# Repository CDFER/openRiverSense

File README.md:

**openRiverSense - Water Quality Tester**
=====================================

### Overview

### Features

### Assembly

### Usage

### Improvements for V2

* Reduce interference between Battery Charging and GPS Antenna
* Backlight powered by CC buck power source?
* Better Shielding on Screen SPI bus to enable reliable 80Mhz bus speeds
* Improve GPS RTC backup power source (CR2032, direct from Lithium-ion)?

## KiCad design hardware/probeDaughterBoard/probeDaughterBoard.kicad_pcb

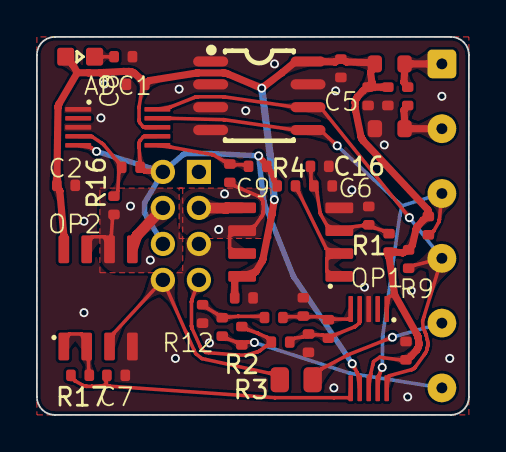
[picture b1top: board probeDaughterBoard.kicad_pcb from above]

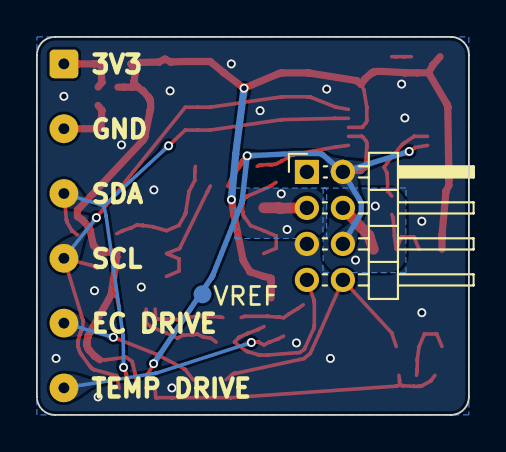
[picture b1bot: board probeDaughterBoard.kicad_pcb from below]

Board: 2 copper layers, 24.0 x 21.0 mm, 41 parts (2 on the bottom side), 25 nets.

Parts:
ADC1, ADC2: ADS1015; MSOP-10_L3.0-W3.0-P0.50-LS5.0-BL
C1, C2, C3, C5, C6: 100nF; 0402_1005Metric
C4: 0402,10uF,6.3V,X5R; 0402_1005Metric
C7, C9, C11: 0402,20pF,50V,C0G; 0402_1005Metric
C8, C12: 0402,100nF,16V,X7R; 0402_1005Metric
C10, C16: 0402,1uF,25V,X5R; 0402_1005Metric
C13: 0402,220nF,16V,X7R; 0402_1005Metric
C14, C15: 0402,22nF,50V,X7R; 0402_1005Metric
EEPROM1: M24C64-RMN6TP; SOIC-8_L5.0-W4.0-P1.27-LS6.0-BL
FB1, FB2: 0603,200mA; 0603_1608Metric
J1: Conn_02x04_Odd_Even; PinHeader_2x04_P2.00mm_Horizontal
J4: Conn_01x06; SolderWire-0.1sqmm_1x06_P3.6mm_D0.4mm_OD1mm
LED1: 0603,Green; LED0603
OP1, OP2: MCP6002; SOIC-8_L4.9-W3.9-P1.27-LS6.0-BL
R1: 0402,2.2k; 0402_1005Metric
R2, R11, R12: 0402,10k; 0402_1005Metric
R3: 0805,470k; 0805_2012Metric
R4, R13, R14, R15, R16, R17: 0402,100; 0402_1005Metric
R5: 0402,47k; 0402_1005Metric
R6: 0402,12k; 0402_1005Metric
R9, R10: 0402,4.7k; 0402_1005Metric

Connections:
+3.3V: ADC1.8 (VDD), ADC2.1 (ADDR), ADC2.8 (VDD), C1.1, C2.1, C3.1, C5.1, C8.1, C10.1, C12.1, EEPROM1.8 (VCC), FB1.1, LED1.2 (A), OP1.8 (+VDD), OP2.8 (+VDD), R6.1, R9.1, R10.1
/3V3_IN: C4.1, FB1.2, J4.1
/EC_DRIVE: J4.5, R3.1
/EC_IN: J1.8, OP2.3 (+), R3.2
/EC_OUT: ADC2.6 (AIN2), C7.1, R17.2
/GND_IN: C4.2, FB2.2, J4.2
/ORP_IN: J1.4, OP2.5 (+)
/ORP_OUT: ADC1.4 (AIN0), C11.1, R16.2
/ORP_RING: OP2.6 (-), OP2.7, R16.1
/PH_IN: J1.3, OP1.5 (+)
/PH_OUT: ADC1.6 (AIN2), C9.1, R15.2
/PH_RING: OP1.6 (-), OP1.7, R15.1
/SCL: ADC1.10 (SCL), ADC2.10 (SCL), EEPROM1.6 (SCL), J4.4, R9.2
/SDA: ADC1.9 (SDA), ADC2.9 (SDA), EEPROM1.5 (SDA), J4.3, R10.2
/TEMP_DRIVE: J4.6, R2.1, R11.1
/TEMP_IN: J1.7, R2.2, R14.1
/TEMP_REF: R11.2, R12.1, R13.1
/VREF: ADC1.5 (AIN1), ADC1.7 (AIN3), ADC2.7 (AIN3), C9.2, C11.2, J1.2, J1.6, R4.2
GND: ADC1.1 (ADDR), ADC1.3 (GND), ADC2.3 (GND), C1.2, C2.2, C3.2, C5.2, C6.2, C7.2, C8.2, C10.2, C12.2, C14.2, C15.1, C16.2, EEPROM1.1 (A0), EEPROM1.2 (A1), EEPROM1.3 (A2), EEPROM1.4 (VSS), EEPROM1.7 (#WC), FB2.1, J1.5, OP1.4 (-VSS), OP2.4 (-VSS), R1.2, R5.2, R12.2
unnamed: ADC2.4 (AIN0), C13.1, C15.2, R14.2
unnamed: ADC2.5 (AIN1), C13.2, C14.1, R13.2
unnamed: C6.1, C16.1, OP1.3 (+), R1.1, R6.2
unnamed: LED1.1 (C), R5.1
unnamed: OP1.1, OP1.2 (-), R4.1
unnamed: OP2.1, OP2.2 (-), R17.1

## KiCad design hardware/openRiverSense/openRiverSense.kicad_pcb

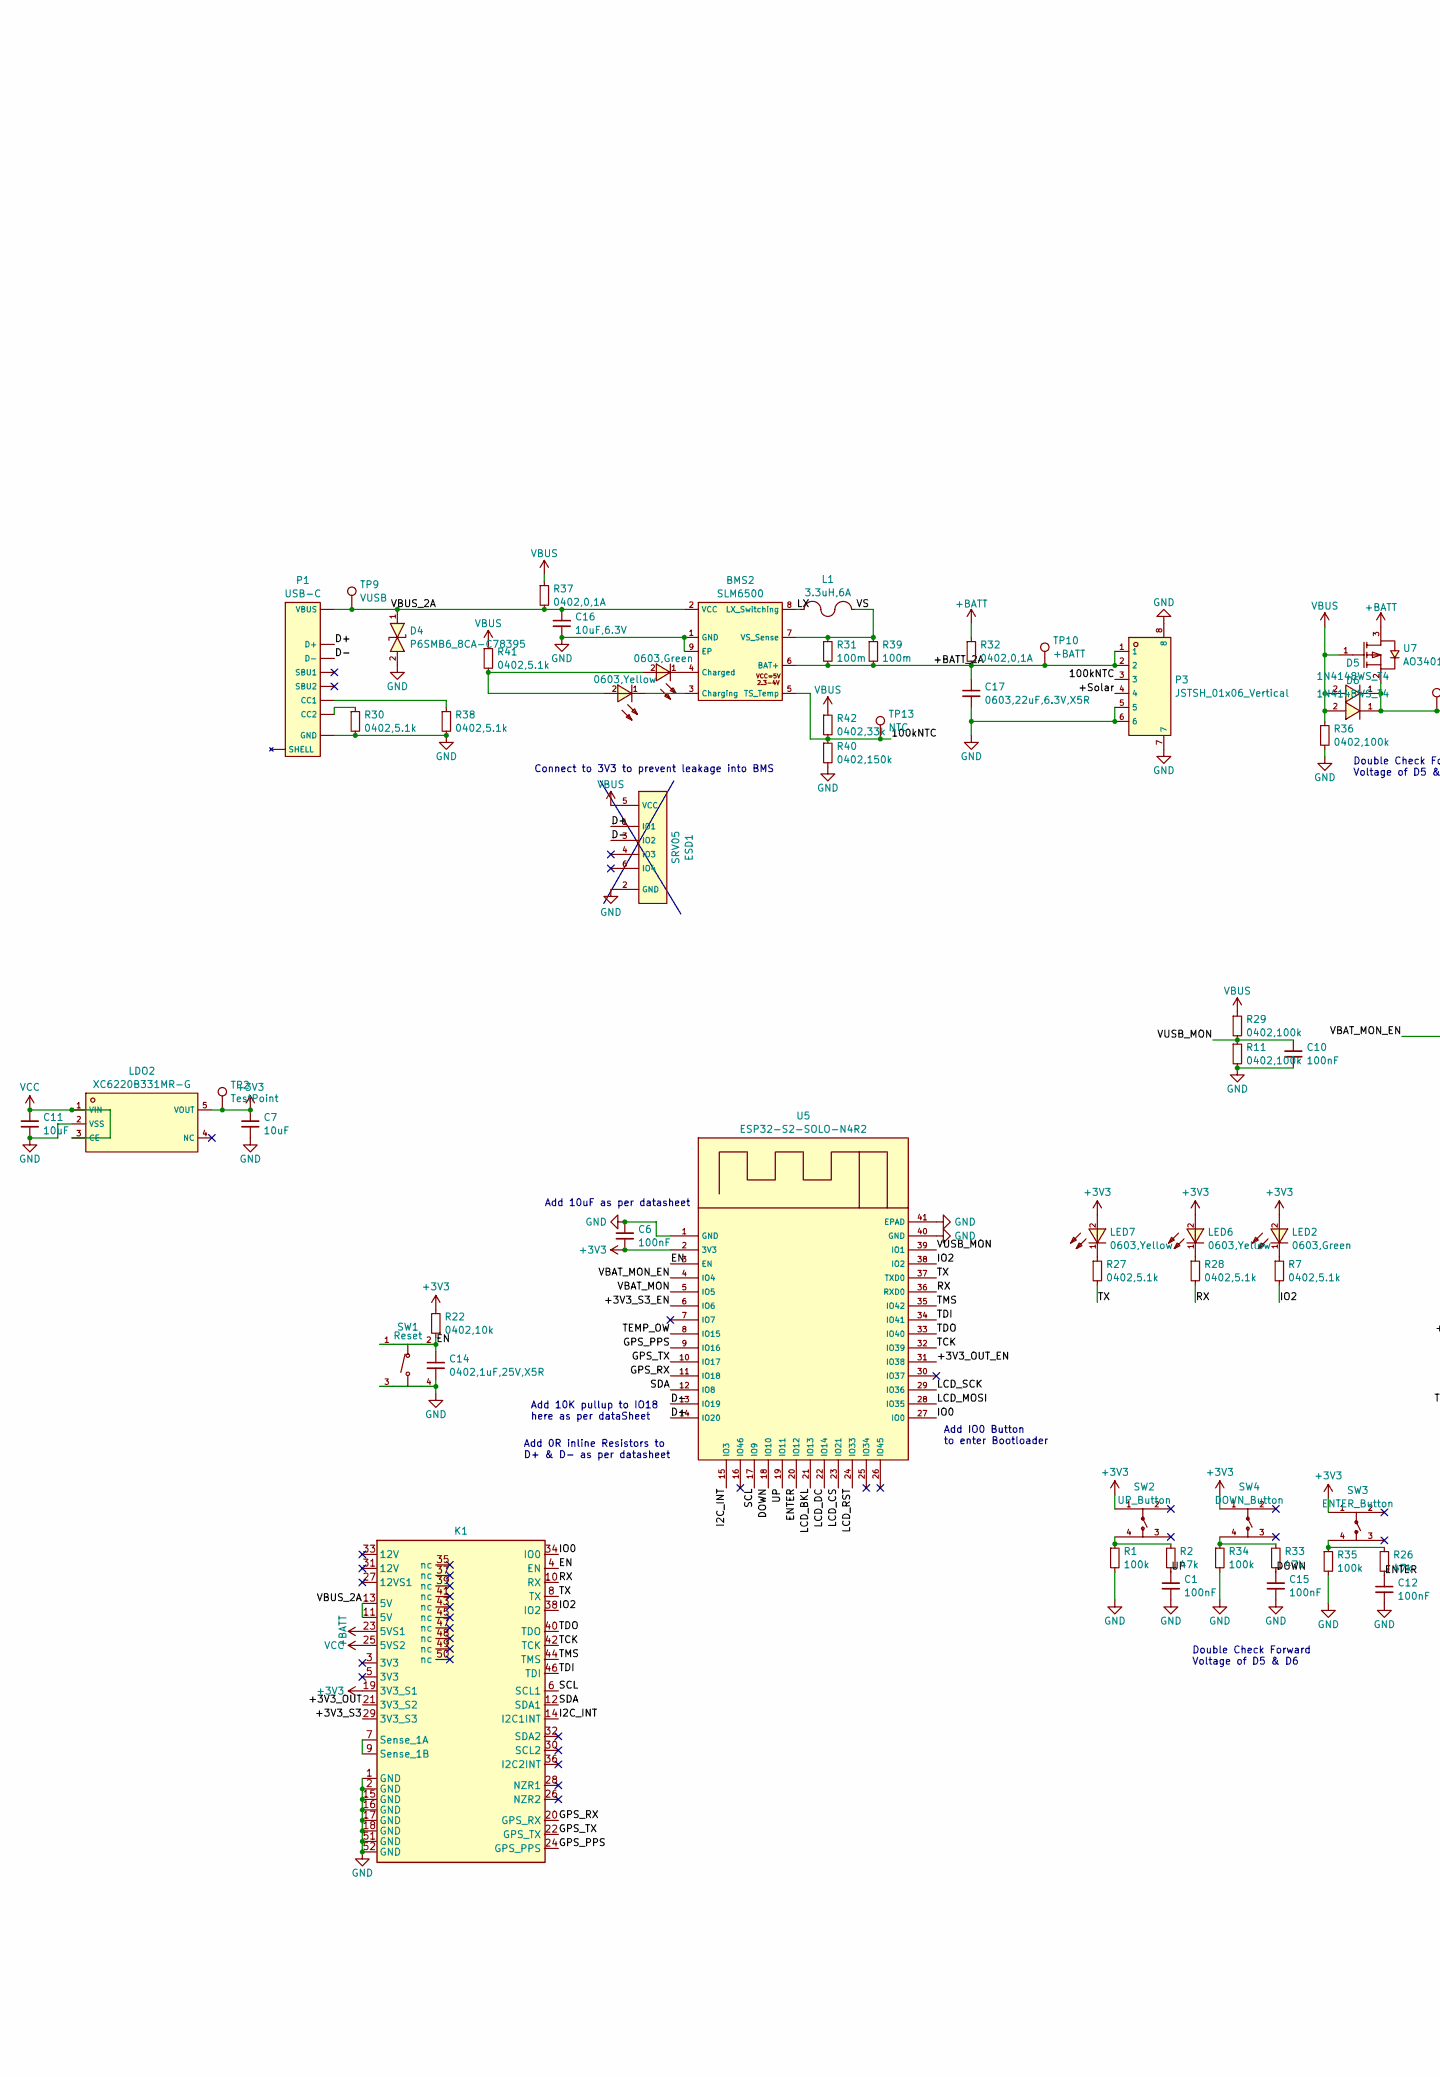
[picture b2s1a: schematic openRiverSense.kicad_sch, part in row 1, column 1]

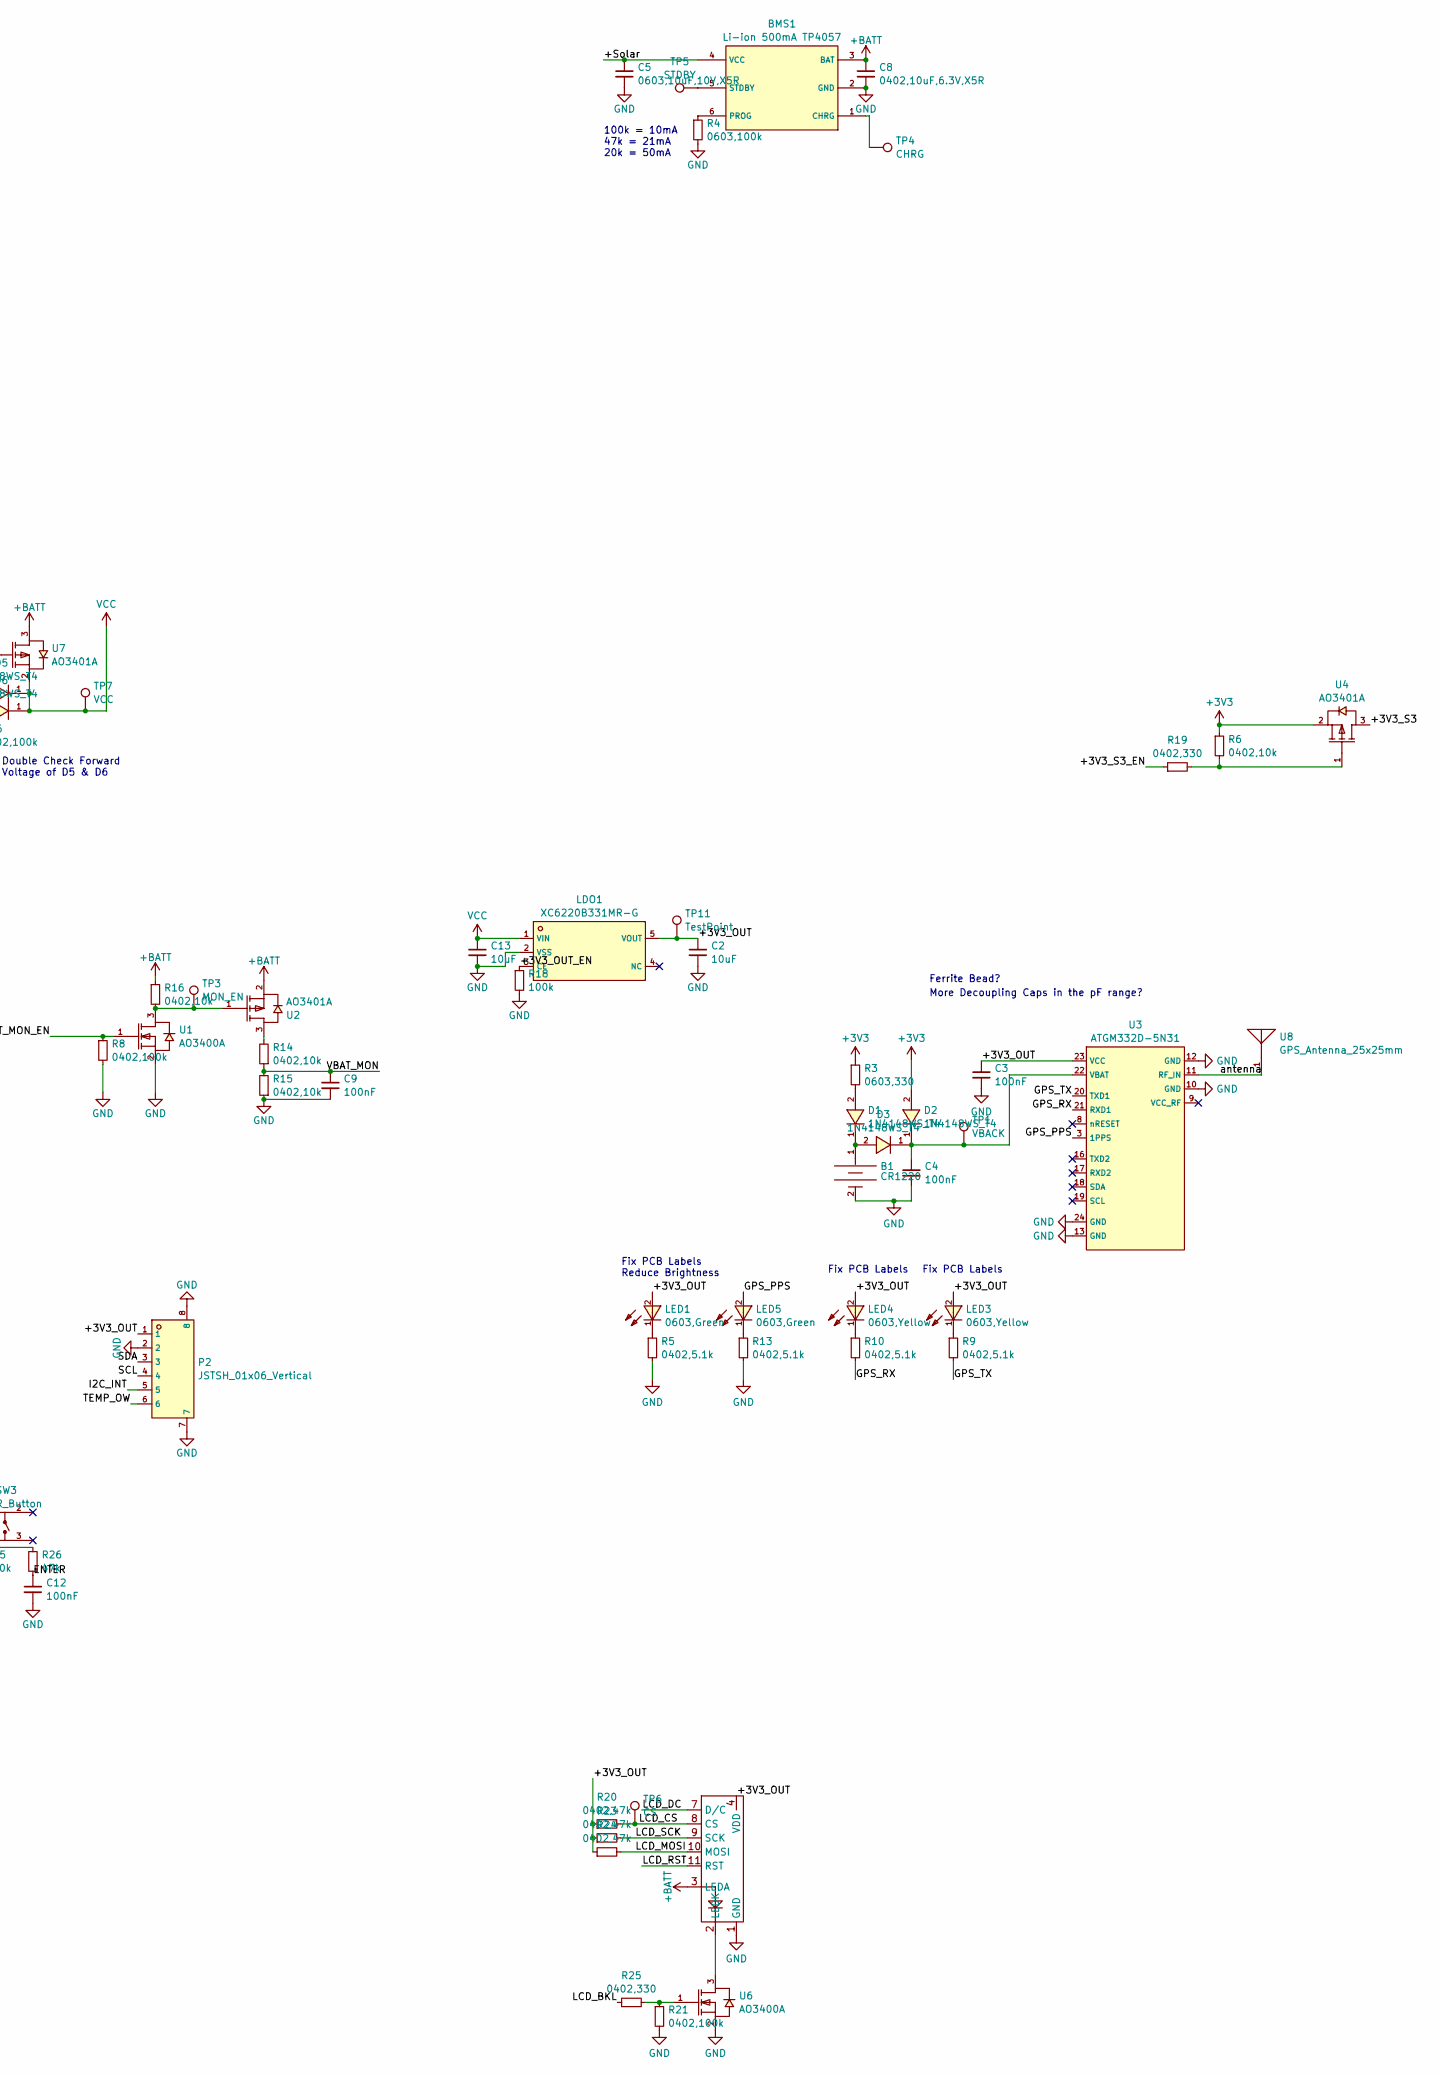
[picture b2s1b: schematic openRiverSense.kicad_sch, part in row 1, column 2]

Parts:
B1: CR1220; BAT-SMD_BS-12-B2AA002; LCSC C964721
BMS1: Li-ion 500mA TP4057; SOT-23-6_L2.9-W1.6-P0.95-LS2.8-BL; LCSC C12044
BMS2: SLM6500; SOP-8_L4.9-W3.9-P1.27-LS6.0-BL-EP; LCSC C130315
C1, C3, C4, C6, C9, C10, C12, C15: 100nF; 0402_1005Metric; MFGPN CL05B104KO5NNNC; LCSC C1525
C2, C7, C11, C13: 10uF; 0402_1005Metric; MFGPN CL05A106MQ5NUNC; LCSC C15525
C5: 0603,10uF,10V,X5R; 0603_1608Metric; MFGPN CL10A106KP8NNNC; LCSC C19702
C8: 0402,10uF,6.3V,X5R; 0402_1005Metric; MFGPN CL05A106MQ5NUNC; LCSC C15525
C14: 0402,1uF,25V,X5R; 0402_1005Metric; MFGPN CL05A105KA5NQNC; LCSC C52923
C16: 10uF,6.3V; 0402_1005Metric; MFGPN CL05A106MQ5NUNC; LCSC C15525
C17: 0603,22uF,6.3V,X5R; 0603_1608Metric; MFGPN CL10A226MQ8NRNC; LCSC C59461
D1, D2, D3, D5, D6: 1N4148WS_T4; SOD-323_L1.8-W1.3-LS2.5-RD; LCSC C2128
D4: P6SMB6_8CA-C78395; SMB_L4.6-W3.6-LS5.3-BI; LCSC C78395
ESD1: SRV05; SOT-23-6_L2.9-W1.6-P0.95-LS2.8-BR; LCSC C85364
K1: mpcie-full-card
L1: 3.3uH,6A; IND-SMD_L7.3-W6.8; LCSC C394166
LDO1, LDO2: XC6220B331MR-G; SOT-25_L3.0-W1.6-P0.95-LS2.8-TL; LCSC C86534
LED1, LED2, LED5, LED9: 0603,Green; LED0603; LCSC C72043
LED3, LED4, LED6, LED7, LED8: 0603,Yellow; LED0603; LCSC C72038
P1: USB-C; USB-C-SMD_G-SWITCH_GT-USB-7010ASV; LCSC C2988369
P2, P3: JSTSH_01x06_Vertical; CONN-SMD_6P-P1.00_DEALON_1.0-6PS; LCSC C2904988
R1, R18, R34, R35: 100k; 0402_1005Metric; MFGPN 0402WGF1003TCE; LCSC C25741
R2, R26, R33: 47k; 0402_1005Metric; MFGPN 0402WGF4702TCE; LCSC C25792
R3: 0603,330; 0603_1608Metric; MFGPN 0603WAF3300T5E; LCSC C23138
R4: 0603,100k; 0603_1608Metric; MFGPN 0603WAF1003T5E; LCSC C25803
R5, R7, R9, R10, R13, R27, R28, R30, R38, R41: 0402,5.1k; 0402_1005Metric; MFGPN 0402WGF5101TCE; LCSC C25905
R6, R14, R15, R16, R22: 0402,10k; 0402_1005Metric; MFGPN 0402WGF1002TCE; LCSC C25744
R8, R11, R21, R29, R36: 0402,100k; 0402_1005Metric; MFGPN 0402WGF1003TCE; LCSC C25741
R19, R25: 0402,330; 0402_1005Metric; MFGPN 0402WGF3300TCE; LCSC C25104
R20, R23, R24: 0402,47k; 0402_1005Metric; MFGPN 0402WGF4702TCE; LCSC C25792
R31, R39: 100m; 1206_3216Metric; MFGPN 1206W4F100LT5E; LCSC C25334
R32, R37: 0402,0,1A; 0402_1005Metric; MFGPN 0402WGF0000TCE; LCSC C17168
R40: 0402,150k; 0402_1005Metric; MFGPN 0402WGF1503TCE; LCSC C25755
R42: 0402,33k; 0402_1005Metric; MFGPN 0402WGF3302TCE; LCSC C25779
SW1: Reset; SW-SMD_4P-L5.1-W5.1-P3.70-LS6.5-TL-2; LCSC C318884
SW2: UP_Button; SW-TH_4P-L12.0-W12.0-P5.00-LS12.5-EH; LCSC C718965
SW3: ENTER_Button; SW-TH_4P-L12.0-W12.0-P5.00-LS12.5-EH; LCSC C718965
SW4: DOWN_Button; SW-TH_4P-L12.0-W12.0-P5.00-LS12.5-EH; LCSC C718965
TFT1: IPS Display
TP1: VBACK; TestPoint_Pad_D1.0mm
TP2, TP11: TestPoint; TestPoint_Pad_D1.0mm
TP3: MON_EN; TestPoint_Pad_D1.0mm
TP4: CHRG; TestPoint_Pad_D1.0mm
TP5: STDBY; TestPoint_Pad_D1.0mm
TP6: CS; TestPoint_Pad_D1.0mm
TP7: VCC; TestPoint_Pad_D1.0mm
TP9: VUSB; TestPoint_Pad_D1.0mm
TP10: +BATT; TestPoint_Pad_D1.0mm
TP13: NTC; TestPoint_Pad_D1.0mm
U1, U6: AO3400A; SOT-23-3_L2.9-W1.6-P1.90-LS2.8-BR; LCSC C20917
U2, U4, U7: AO3401A; SOT-23_L2.9-W1.3-P1.90-LS2.4-BR; LCSC C15127
U3: ATGM332D-5N31; GSM-SMD_ATGM332D-5N31; LCSC C128659
U5: ESP32-S2-SOLO-N4R2; WIRELM-SMD_ESP32-S3-WROOM-1; LCSC C3013947
U8: GPS_Antenna_25x25mm; ANT-TH_KH-GPS252504-WY; LCSC C962216

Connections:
+3V3: C6.2, C7.1, D2.2 (A), K1.19 (3V3_S1), LDO2.5 (VOUT), LED2.2 (A), LED6.2 (A), LED7.2 (A), R3.1, R6.1, R22.2, SW2.1, SW3.1, SW4.1, TP2.1, U4.2 (S), U5.2 (3V3)
+BATT: BMS1.3 (BAT), C8.1, K1.23 (5VS1), R16.1, R32.1, TFT1.3 (LEDA), U2.2 (S), U7.3 (D)
/100kNTC: BMS2.5 (TS_Temp), P3.3, R40.1, R42.2, TP13.1
/+3V3_OUT: C2.1, C3.1, K1.21 (3V3_S2), LDO1.5 (VOUT), LED1.2 (A), LED3.2 (A), LED4.2 (A), P2.1, R20.1, R23.1, R24.1, TFT1.4 (VDD), TP11.1, U3.23 (VCC)
/+3V3_OUT_EN: LDO1.3 (CE), R18.1, U5.31 (IO38)
/+3V3_S3: K1.29 (3V3_S3), U4.3 (D)
/+3V3_S3_EN: R19.1, U5.6 (IO6)
/+BATT_2A: BMS2.6 (BAT+), C17.1, P3.1, P3.2, R31.2, R32.2, R39.2, TP10.1
/+Solar: BMS1.4 (VCC), C5.1, P3.4
/D+: ESD1.1 (IO1), P1.DP (D+), U5.14 (IO20)
/D-: ESD1.3 (IO2), P1.DN (D-), U5.13 (IO19)
/DOWN: C15.1, R33.1, U5.18 (IO10)
/EN: C14.1, K1.4 (EN), R22.1, SW1.1 (A), SW1.2 (B), U5.3 (EN)
/ENTER: C12.1, R26.1, U5.20 (IO12)
/GPS_PPS: K1.24 (GPS_PPS), LED5.2 (A), U3.3 (1PPS), U5.9 (IO16)
/GPS_RX: K1.20 (GPS_RX), R10.2, U3.21 (RXD1), U5.11 (IO18)
/GPS_TX: K1.22 (GPS_TX), R9.2, U3.20 (TXD1), U5.10 (IO17)
/I2C_INT: K1.14 (I2C1INT), P2.5, U5.15 (IO3)
/IO0: K1.34 (IO0), U5.27 (IO0)
/IO2: K1.38 (IO2), R7.2, U5.38 (IO2)
/LCD_BKL: R25.1, U5.21 (IO13)
/LCD_CS: R20.2, TFT1.8 (CS), TP6.1, U5.23 (IO21)
/LCD_DC: TFT1.7 (D/C), U5.22 (IO14)
/LCD_MOSI: R24.2, TFT1.10 (MOSI), U5.28 (IO35)
/LCD_RST: TFT1.11 (RST), U5.24 (IO33)
/LCD_SCK: R23.2, TFT1.9 (SCK), U5.29 (IO36)
/LX: BMS2.8 (LX_Switching), L1.1
/RX: K1.10 (RX), R28.2, U5.36 (RXD0)
/SCL: K1.6 (SCL1), P2.4, U5.17 (IO9)
/SDA: K1.12 (SDA1), P2.3, U5.12 (IO8)
/TCK: K1.42 (TCK), U5.32 (IO39)
/TDI: K1.46 (TDI), U5.34 (IO41)
/TDO: K1.40 (TDO), U5.33 (IO40)
/TEMP_OW: P2.6, U5.8 (IO15)
/TMS: K1.44 (TMS), U5.35 (IO42)
/TX: K1.8 (TX), R27.2, U5.37 (TXD0)
/UP: C1.1, R2.1, U5.19 (IO11)
/VBAT_MON: C9.1, R14.1, R15.2, U5.5 (IO5)
/VBAT_MON_EN: R8.1, U1.1 (G), U5.4 (IO4)
/VBUS_2A: BMS2.2 (VCC), C16.1, D4.1, K1.11 (5V), K1.13 (5V), P1.3 (VBUS), R37.2, TP9.1
/VS: BMS2.7 (VS_Sense), L1.2, R31.1, R39.1
/VUSB_MON: C10.1, R11.1, R29.2, U5.39 (IO1)
/antenna: U3.11 (RF_IN), U8.1 (ANT)
GND: B1.2 (-), BMS1.2 (GND), BMS2.1 (GND), BMS2.9 (EP), C1.2, C2.2, C3.2, C4.2, C5.2, C6.1, C7.2, C8.2, C9.2, C10.2, C11.2, C12.2, C13.2, C14.2, C15.2, C16.2, C17.2, D4.2, ESD1.2 (GND), K1.1 (GND), K1.2 (GND), K1.15 (GND), K1.16 (GND), K1.17 (GND), K1.18 (GND), K1.51 (GND), K1.52 (GND), LDO1.2 (VSS), LDO2.2 (VSS), P1.2 (GND), P2.2, P2.7, P2.8, P3.5, P3.6, P3.7, P3.8, R1.2, R4.2, R5.2, R8.2, R11.2, R13.2, R15.1, R18.2, R21.2, R30.2, R34.2, R35.2, R36.2, R38.2, R40.2, SW1.3 (C), SW1.4 (D), TFT1.1 (GND), U1.2 (S), U3.10 (GND), U3.12 (GND), U3.13 (GND), U3.24 (GND), U5.1 (GND), U5.40 (GND), U5.41 (EPAD), U6.2 (S)
unnamed: B1.1 (+), D1.1 (K), D3.2 (A)
unnamed: BMS1.1 (CHRG), TP4.1
unnamed: BMS1.6 (PROG), R4.1
unnamed: BMS1.5 (STDBY), TP5.1
unnamed: BMS2.4 (Charged), LED9.1 (C)
unnamed: BMS2.3 (Charging), LED8.1 (C)
unnamed: D1.2 (A), R3.2
unnamed: C4.1, D2.1 (K), D3.1 (K), TP1.1, U3.22 (VBAT)
unnamed: K1.7 (Sense_1A), K1.9 (Sense_1B)
unnamed: LED1.1 (C), R5.1
unnamed: LED2.1 (C), R7.1
unnamed: LED3.1 (C), R9.1
unnamed: LED4.1 (C), R10.1
unnamed: LED5.1 (C), R13.1
unnamed: LED6.1 (C), R28.1
unnamed: LED7.1 (C), R27.1
unnamed: LED8.2 (A), LED9.2 (A), R41.2
unnamed: P1.CC1, R38.1
unnamed: P1.CC2, R30.1
unnamed: R1.1, R2.2, SW2.4
unnamed: R26.2, R35.1, SW3.4
unnamed: R33.2, R34.1, SW4.4
unnamed: TFT1.2 (LEDK), U6.3 (D)
unnamed: R16.2, TP3.1, U1.3 (D), U2.1 (G)
unnamed: R14.2, U2.3 (D)
unnamed: R6.2, R19.2, U4.1 (G)
unnamed: R21.1, R25.2, U6.1 (G)
VBUS: D5.2 (A), D6.2 (A), ESD1.5 (VCC), R29.1, R36.1, R37.1, R41.1, R42.1, U7.1 (G)
VCC: C11.1, C13.1, D5.1 (K), D6.1 (K), K1.25 (5VS2), LDO1.1 (VIN), LDO2.1 (VIN), LDO2.3 (CE), TP7.1, U7.2 (S)

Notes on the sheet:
Add 10K pullup to IO18 here as per dataSheet
Double Check Forward Voltage of D5 & D6
Add 10uF as per datasheet
More Decoupling Caps in the pF range?
Fix PCB Labels Reduce Brightness
Fix PCB Labels
Add 0R inline Resistors to D+ & D- as per datasheet
Ferrite Bead?
Add IO0 Button to enter Bootloader
Connect to 3V3 to prevent leakage into BMS
100k = 10mA 47k = 21mA 20k = 50mA

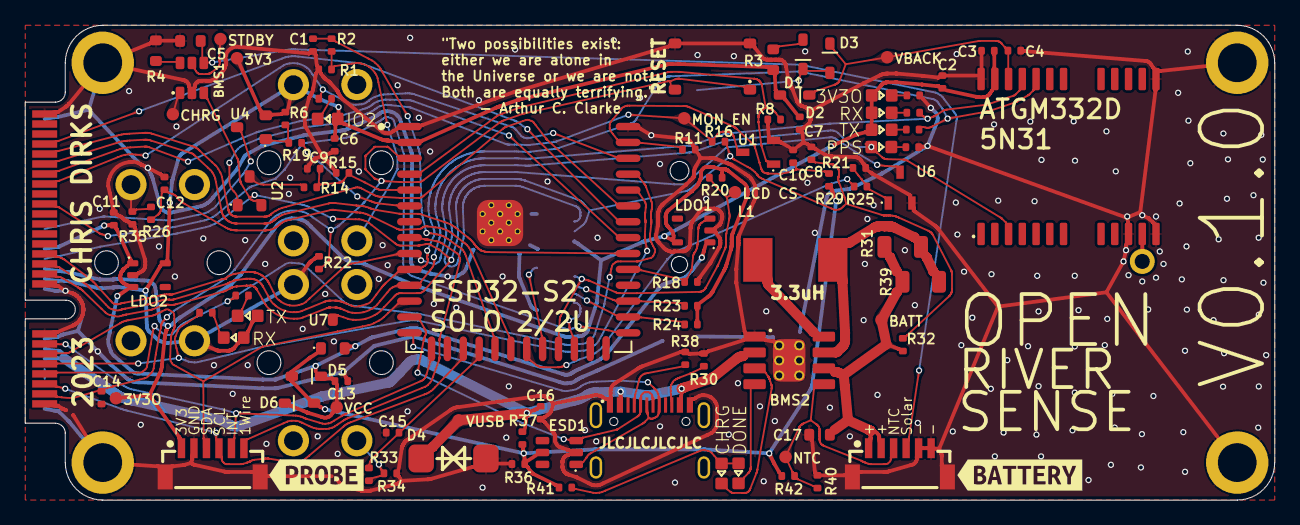
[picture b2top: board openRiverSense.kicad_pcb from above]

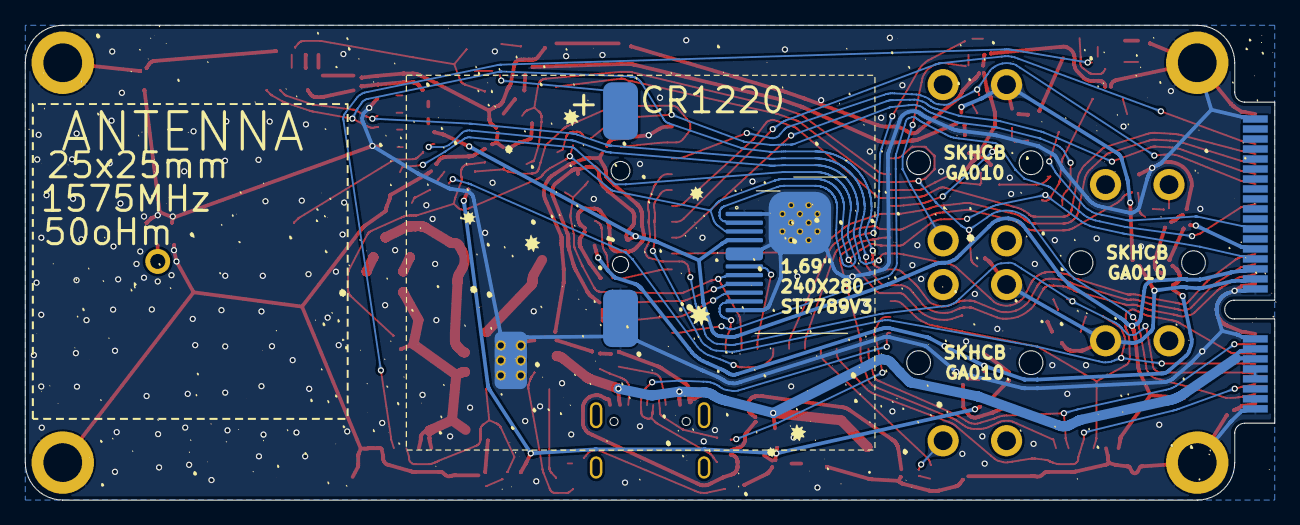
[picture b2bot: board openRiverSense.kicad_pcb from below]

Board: 2 copper layers, 100.0 x 38.0 mm, 109 parts (7 on the bottom side), 73 nets.

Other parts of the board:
kibuzzard-1: G***; kibuzzard-651F6E89
kibuzzard-2: G***; kibuzzard-651F6E67

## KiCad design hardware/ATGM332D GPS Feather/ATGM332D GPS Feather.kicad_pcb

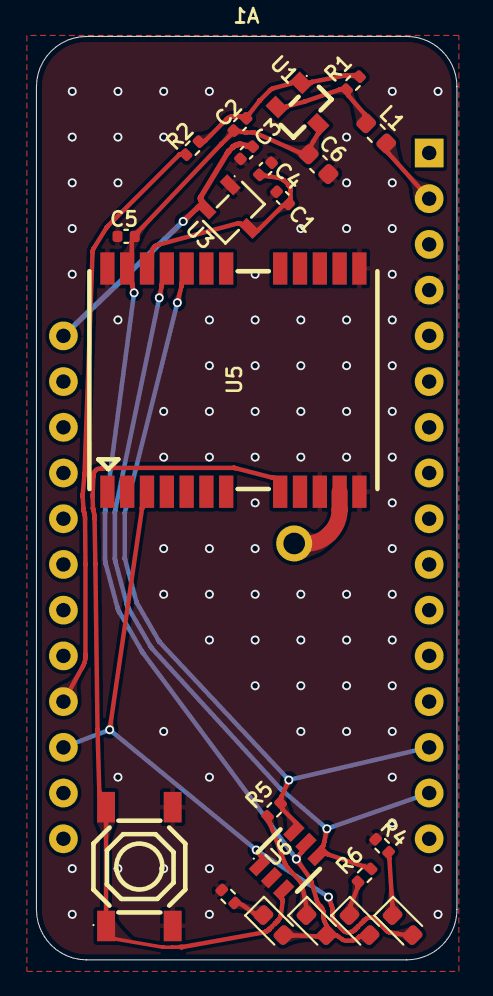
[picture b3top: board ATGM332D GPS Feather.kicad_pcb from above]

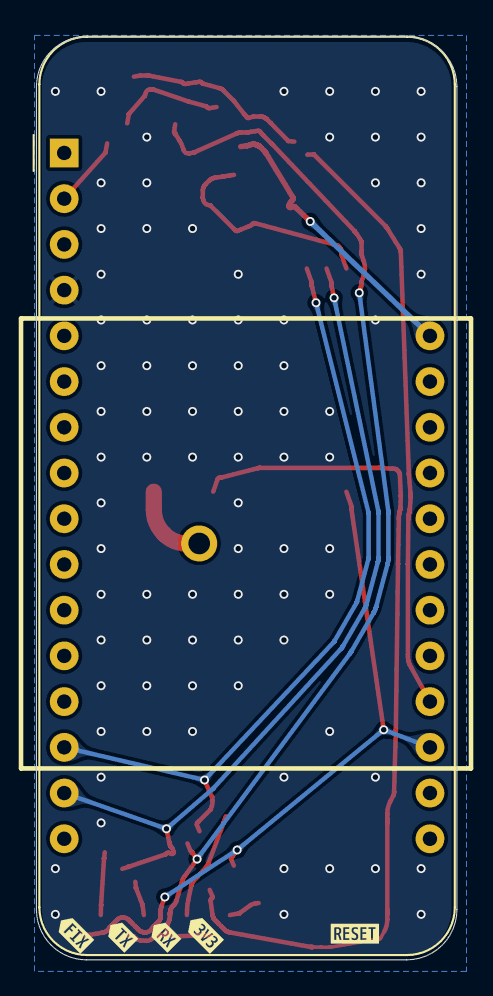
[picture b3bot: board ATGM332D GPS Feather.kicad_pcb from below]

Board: 2 copper layers, 23.4 x 51.3 mm, 30 parts (7 on the bottom side), 17 nets.

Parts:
A1: Adafruit_Feather_Generic; Adafruit_Feather
C1, C3: 0402,10uF,6.3V,X5R; C_0402_1005Metric
C2, C4, C5: 0402,100nF,16V,X7R; C_0402_1005Metric
C6: 0603,22uF,6.3V,X5R; C_0603_1608Metric
L1: GZ1608D601TF; L_0603_1608Metric
LED1, LED2: Green; LED_0603_1608Metric
LED3, LED4: Yellow; LED_0603_1608Metric
R1, R3: 0402,100k; R_0402_1005Metric
R2: 0402,10k; R_0402_1005Metric
R4, R5, R6: 0402,47k; R_0402_1005Metric
U1: AO3401A; SOT-23_L2.9-W1.3-P1.90-LS2.4-BR
U2: KH-GPS252504-WY; ANT-TH_KH-GPS252504-WY
U3: XC6206P332MR; SOT-23-3_L2.9-W1.6-P1.90-LS2.8-BR
U4: TS-1187A-B-A-B; SW-SMD_4P-L5.1-W5.1-P3.70-LS6.5-TL-2
U5: ATGM332D-5N31; GSM-SMD_ATGM332D-5N31
U6: SRV05-4-P-T7; SOT-23-6_L2.9-W1.6-P0.95-LS2.8-BR
kibuzzard-1: G***; kibuzzard-64D975BA
kibuzzard-2: G***; kibuzzard-64D975C8
kibuzzard-3: G***; kibuzzard-64D9774E
kibuzzard-4: G***; kibuzzard-64D97593
kibuzzard-5: G***; kibuzzard-64D975D5
x: x; de35f500-bef9-453f-b4cc-6297b0a98bec

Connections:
+3.3V: C2.2, C5.1, C6.1, LED1.2 (A), LED3.2 (A), LED4.2 (A), U1.3 (D), U5.23 (VCC), U6.5
+BATT: A1.28 (VBAT), C3.1, U3.2 (Vin)
/Antenna: U2.1 (ANT), U5.11 (RF_IN)
/GPS_1PPS: A1.19 (D0), LED2.2 (A), U5.3 (1PPS), U6.1
/GPS_EN: A1.20 (D1), R2.1
/GPS_RX: A1.15 (TX), R6.2, U5.21 (RXD1), U6.4
/GPS_TX: A1.14 (RX), R5.2, U5.20 (TXD1), U6.6
/RESET: U4.1 (A), U4.2 (B), U5.8 (nRESET), U6.3
/VBAT: C1.1, C4.1, U3.3 (Vout), U5.22 (VBAT)
GND: A1.4 (GND), C1.2, C3.2, C4.2, C5.2, C6.2, R3.2, R4.2, U3.1 (GND), U4.3 (C), U4.4 (D), U5.10 (GND), U5.12 (GND), U5.13 (GND), U5.24 (GND), U6.2
unnamed: A1.2 (3V3), L1.2
unnamed: LED1.1 (C), R3.1
unnamed: LED2.1 (C), R4.1
unnamed: LED3.1 (C), R5.1
unnamed: LED4.1 (C), R6.1
unnamed: C2.1, R1.2, R2.2, U1.1 (G)
unnamed: L1.1, R1.1, U1.2 (S)

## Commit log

2023-07-30 setup KiCad
2023-08-31 - alpha board design - UVGL added
2023-08-31 fix .gitmodules
2023-08-31 - add gps - add usb Storage
2023-09-05 -config updates -gps testing
2023-09-06 first pass gui
2023-09-06 refactor into headers fix dateTime
2023-09-18 Add Base Menu System
2023-09-22 GPS deepSleep implementation
2023-10-18 PCB Design Move to UF2 bootloader Move to Adafruit TinyUSB for mass storage Update Formatting Flip UI orientation Change to PWM Backlight
2023-10-22 - setup state machine - add adafruit.io - fix battery soc calculation - increase gps baud rate
2023-10-24 basic sensor setup
2023-10-25 bugfix adc
2023-10-28 add basic TDS functionality
2023-10-29 rewrite for non blocking menu
2023-10-31 - rewrite gui - add calibration to gui - add export/import to eeprom
2023-11-01 - add calibration order & points config - add record and save to file - add TDS calibrate
2023-11-02 rewrite main state machine
2024-08-28 -added CAD models -moved to KiCAD 8.0 -clang formatting -rebuild sensor calibration -add logging and analytics file -added adaptive backlight -added work hours for gps sync
